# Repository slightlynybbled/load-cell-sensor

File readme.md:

# Purpose #

This repository is to document the hardware to be used to create a load cell monitoring board.
Details may be found at [for(embed)](http://www.forembed.com/category/load-cell-sensor.html).

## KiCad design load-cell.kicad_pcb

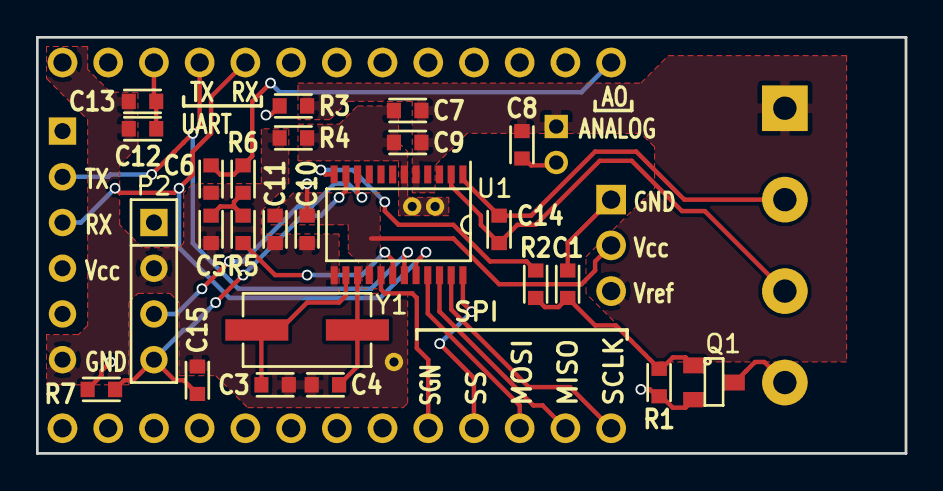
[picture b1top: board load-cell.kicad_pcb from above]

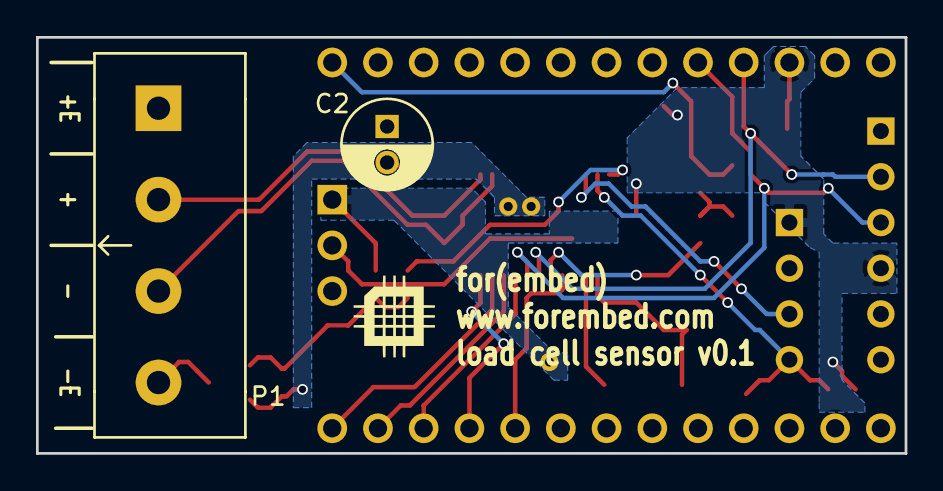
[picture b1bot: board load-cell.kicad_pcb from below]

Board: 2 copper layers, 48.3 x 23.1 mm, 31 parts (2 on the bottom side), 23 nets.

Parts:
C1, C5, C6, C7, C8, C9, C10, C11, C12, C13, C14: 100nF; SM_0603
C2: 100uF 10V; C_Radial_D5_L11_P2
C3, C4: 18pF; SM_0603
C15: 2.2nF; SM_0603
P1: CONN_01X04; CONN_1x4_OSTTC042162
P2: CONN_01X04; CON_1x4_0.1in
P3, P4: CONN_01X13; CON_1x13_0.1in_no_silk
P5: CONN_01X06; CON_1x6_0.1in_no_silk
P6: CONN_01X03; CON_1x3_0.1in_no_silk
Q1: Q_NMOS_GSD; SOT-23
R1, R5, R6: 10k; SM_0603
R2, R3, R4: 10; SM_0603
R7: 47k; SM_0603
U1: msp430afe251; TSSOP-24
Y1: 12MHz; XTAL_ABLS7M

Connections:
+3V3: C10.1, C11.1, C12.1, C13.1, P2.1, P3.11, P5.4, P6.2, R3.1, R7.2, U1.16
/ANO: C6.1, P3.1, R6.2
/PWMO: R5.1, U1.18
/SBWDIO: C15.1, P2.4, R7.1, U1.11
/SBWTCK: P2.3, U1.10
/SENSE+: C14.1, P1.2, U1.1
/SENSE-: C14.2, P1.3, U1.2
/SIGN: P4.9, U1.17
/SIMO: P4.11, U1.21
/SOMI: P4.12, U1.22
/STE0: P4.10, U1.24
/UCLK0: P4.13, U1.23
/URXD0: P3.9, P5.3, U1.20
/UTXD0: P3.10, P5.2, U1.19
GND: C1.2, C3.2, C4.2, C5.2, C6.2, C10.2, C11.2, C12.2, C13.2, C15.2, P2.2, P3.13, P5.6, P6.1, R4.1, U1.13
GNDA: C2.2, C7.2, C8.2, C9.2, Q1.2, R1.1, R4.2, U1.6
unnamed: C1.1, Q1.1, R1.2, R2.2
unnamed: C3.1, U1.14, Y1.2
unnamed: C4.1, U1.15, Y1.1
unnamed: C5.1, R5.2, R6.1
unnamed: P1.4, Q1.3
unnamed: R2.1, U1.12
VAA: C2.1, C7.1, C8.1, C9.1, P1.1, P6.3, R3.2, U1.5

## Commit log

2016-08-02 Finalizing release 0.1 files
2016-08-03 Added readme
